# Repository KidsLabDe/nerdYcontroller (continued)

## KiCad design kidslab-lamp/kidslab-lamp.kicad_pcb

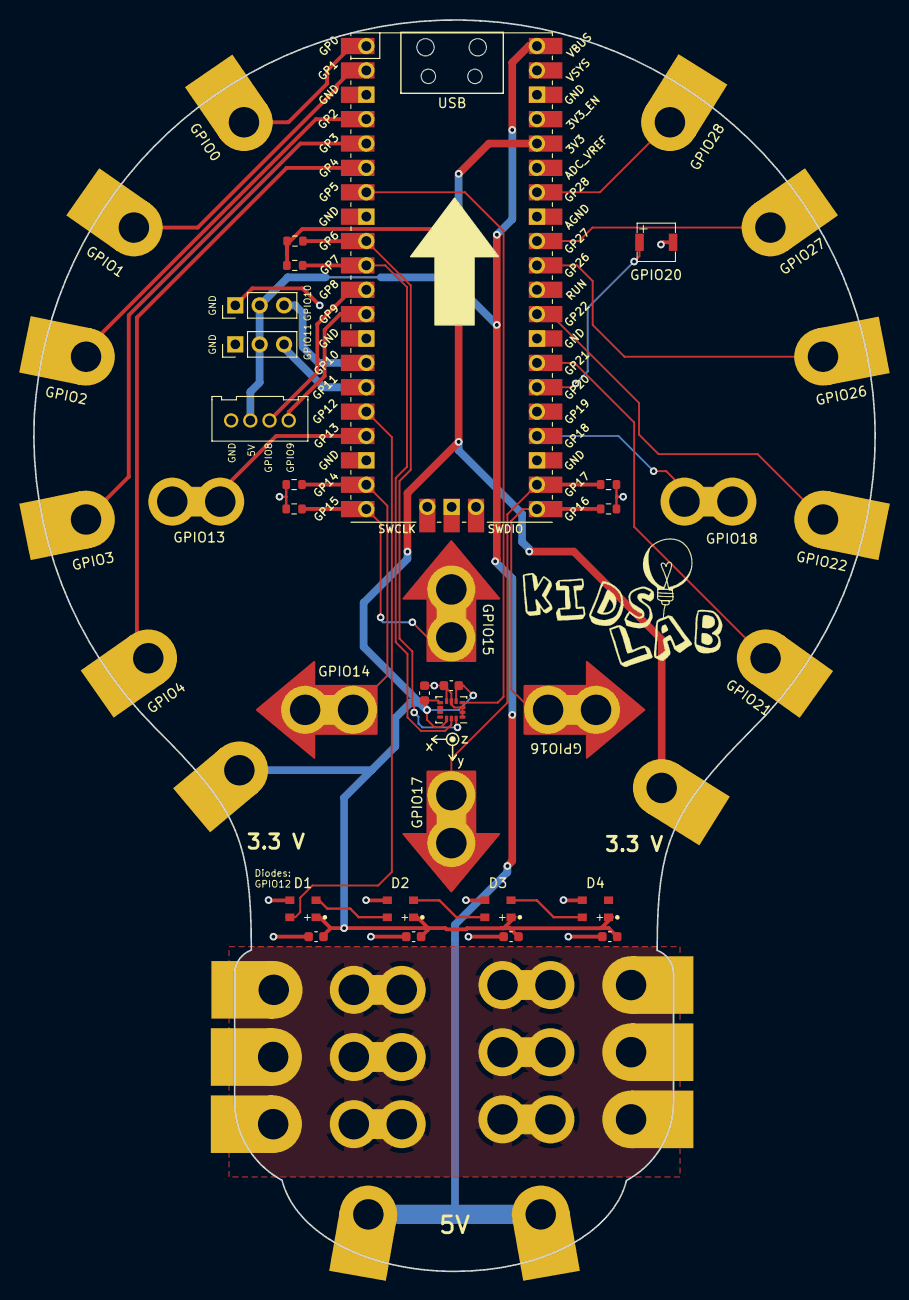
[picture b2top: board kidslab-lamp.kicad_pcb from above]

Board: 2 copper layers, 87.7 x 130.4 mm, 54 parts (0 on the bottom side), 31 nets.

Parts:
B1, B2, B3, B4, B5, B6: kroko_board; KrokoConnector
BZ1: Buzzer-FUET-4020
C4, C5, C6, C7, C8, C9: 100nF; C_0603_1608Metric
D1, D2, D3, D4: WS2812B-Mini
E30, E31, E32, E33, E34, E35, E37, E38, E39, E40: kroko_edge; Edgeconnector
GPIO0, GPIO1, GPIO2, GPIO3, GPIO4, GPIO21, GPIO22, GPIO26, GPIO27, GPIO28: kroko_edge; Edgeconnector
GPIO13, GPIO18: kroko_board; KrokoConnector
GPIO14, GPIO15, GPIO16, GPIO17: arrow; Kroko_Arrow
J1: HY-4A; HY-4A-THT
J2, J3: pin_header_1x3; PinHeader_1x03_P2.54mm_Vertical
R1, R2, R3, R4: 1M; R_0603_1608Metric
R5, R6: 10k; R_0603_1608Metric
U1: Pico; RPi_Pico_SMD_TH
U2: LSM6DS3TR-C; LGA-14_3x2.5mm_P0.5mm_LayoutBorder3x4y

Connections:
+3V3: C4.1, C5.1, C6.1, C7.1, C8.1, C9.1, D1.1 (VDD), D2.1 (VDD), D3.1 (VDD), D4.1 (VDD), E39.1, E40.1, R5.1, R6.1, U1.36 (3V3), U2.5 (VDDIO), U2.8 (VDD), U2.12 (CS)
+5V: E37.1, E38.1, J1.3, J2.2 (5V), J3.2 (5V), U1.40 (VBUS)
GND: B1.1, B2.1, B3.1, B4.1, B5.1, B6.1, BZ1.2 (+), C4.2, C5.2, C6.2, C7.2, C8.2, C9.2, D1.3 (VSS), D2.3 (VSS), D3.3 (VSS), D4.3 (VSS), E30.1, E31.1, E32.1, E33.1, E34.1, E35.1, J1.4, J2.1 (GND), J3.1 (GND), R1.2, R2.2, R3.2, R4.2, U1.3 (GND), U1.8 (GND), U1.13 (GND), U1.18 (GND), U1.23 (GND), U1.28 (GND), U1.38 (GND), U2.1 (SDO/SA0), U2.2 (SDX), U2.3 (SCX), U2.6 (GND), U2.7 (GND)
GPIO5/INTR: U1.7 (GPIO5), U2.4 (INT1)
GPIO6/SDA1: R5.2, U1.9 (GPIO6), U2.14 (SDA)
GPIO7/SCL1: R6.2, U1.10 (GPIO7), U2.13 (SCL)
GPIO8/GROVE_TX: J1.2, U1.11 (GPIO8)
GPIO9/GROVE_RX: J1.1, U1.12 (GPIO9)
GPIO10: J2.3 (S), U1.14 (GPIO10)
GPIO11: J3.3 (S), U1.15 (GPIO11)
GPIO12: D1.4 (DIN), U1.16 (GPIO12)
GPIO14: GPIO14.1, R2.1, U1.19 (GPIO14)
GPIO15: GPIO15.1, R1.1, U1.20 (GPIO15)
GPIO16: GPIO16.1, R4.1, U1.21 (GPIO16)
GPIO17: GPIO17.1, R3.1, U1.22 (GPIO17)
GPIO20/Buzzer: BZ1.1 (-), U1.26 (GPIO20)
unnamed: D1.2 (DOUT), D2.4 (DIN)
unnamed: D2.2 (DOUT), D3.4 (DIN)
unnamed: D3.2 (DOUT), D4.4 (DIN)
unnamed: GPIO0.1, U1.1 (GPIO0)
unnamed: GPIO1.1, U1.2 (GPIO1)
unnamed: GPIO2.1, U1.4 (GPIO2)
unnamed: GPIO3.1, U1.5 (GPIO3)
unnamed: GPIO4.1, U1.6 (GPIO4)
unnamed: GPIO13.1, U1.17 (GPIO13)
unnamed: GPIO18.1, U1.24 (GPIO18)
unnamed: GPIO21.1, U1.27 (GPIO21)
unnamed: GPIO22.1, U1.29 (GPIO22)
unnamed: GPIO26.1, U1.31 (GPIO26_ADC0)
unnamed: GPIO27.1, U1.32 (GPIO27_ADC1)
unnamed: GPIO28.1, U1.34 (GPIO28_ADC2)

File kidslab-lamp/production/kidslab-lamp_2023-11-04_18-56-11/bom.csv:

Designator,Footprint,Quantity,Value,LCSC Part #
BZ1,Buzzer-FUET-4020,1,Buzzer-FUET-4020,C391027
"C4, C5, C6, C7, C8, C9",0603,6,100nF,C14663
"D1, D2, D3, D4",WS2812B-Mini,4,WS2812B-Mini,C527089
J1,HY-4A-THT,1,HY-4A,C146064
"J2, J3",PinHeader_1x03_P2.54mm_Vertical,2,pin_header_1x3,
"R1, R2, R3, R4",0603,4,1M,C105578
"R5, R6",0603,2,10k,C25804
U2,LGA-14_3x2.5mm_P0.5mm_LayoutBorder3x4y,1,LSM6DS3,C95230

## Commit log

2022-05-11 added outline as footprint to be edited for working edge cout
2022-05-11 same as before
2022-05-18 new pcb outline, added frisbee footprints, smaller PCB, added arrow footprints etc.
2022-05-19 Added svg of the shape of the bulb and the logo in B&W
2022-05-19 added 3.3V rail, replaced GND on bottom with 5V rail added Servo pin header
2022-05-22 Design der Rückseite
2022-05-22 added backside art, LED, and frontside kidslab logo
2022-05-23 finished design, further checks have to be done before ordering
2022-09-11 updated PCB with requested changes
2022-09-12 cleared schematics and exported pdf, fixed some routing issues, generated gerber files
2022-12-11 Minecraft Lautstärke-Wächter
2022-12-11 Image Pfad angepasst
2022-12-13 Update README.md
    visitenkarten infos 👍
2023-01-07 Neues Beispiel: Uhr mit NeoPixel 8x32
2023-11-03 adding components to schematic
2023-11-04 adding layout
2023-11-04 fixing some silkscreen issues
2023-11-15 fixing component attributes, moving v1 gerber files
2023-12-16 ploted schematics
2024-01-05 adding coordinate system for imu, changing imu part, changing touch resitros to pull down
2024-01-08 adding polarity information to silkscreen
2024-02-01 Beispiel Firmware
2024-02-07 neue Beispiele, aufgeräumt
2024-03-10 Anleitung für den Zusammenbau
2024-04-15 - Anleitung & aufgeräumtes NeoPixel Beispiel
2024-05-13 die blinkenlights fliege als firmware
2024-09-16 aktuelle Firmware mit Beispielen
2024-09-17 version mit test-main.py
2024-09-20 Neue Anleitung für den Bausatz / MYS Workshop MakerFestival
2024-10-06 adding new project with USB-C connector and 3V3 LDO
2024-10-07 Adding components to USB-C and 3V3 LDO
2024-10-17 neue firmware mit neuen beispielen
2024-10-24 Deleting backups
2024-10-24 Adding kicad-nerdYController
2024-12-27 firmware für platinen ohne imu
2025-01-08 Adding KiCad files for first controller production.
